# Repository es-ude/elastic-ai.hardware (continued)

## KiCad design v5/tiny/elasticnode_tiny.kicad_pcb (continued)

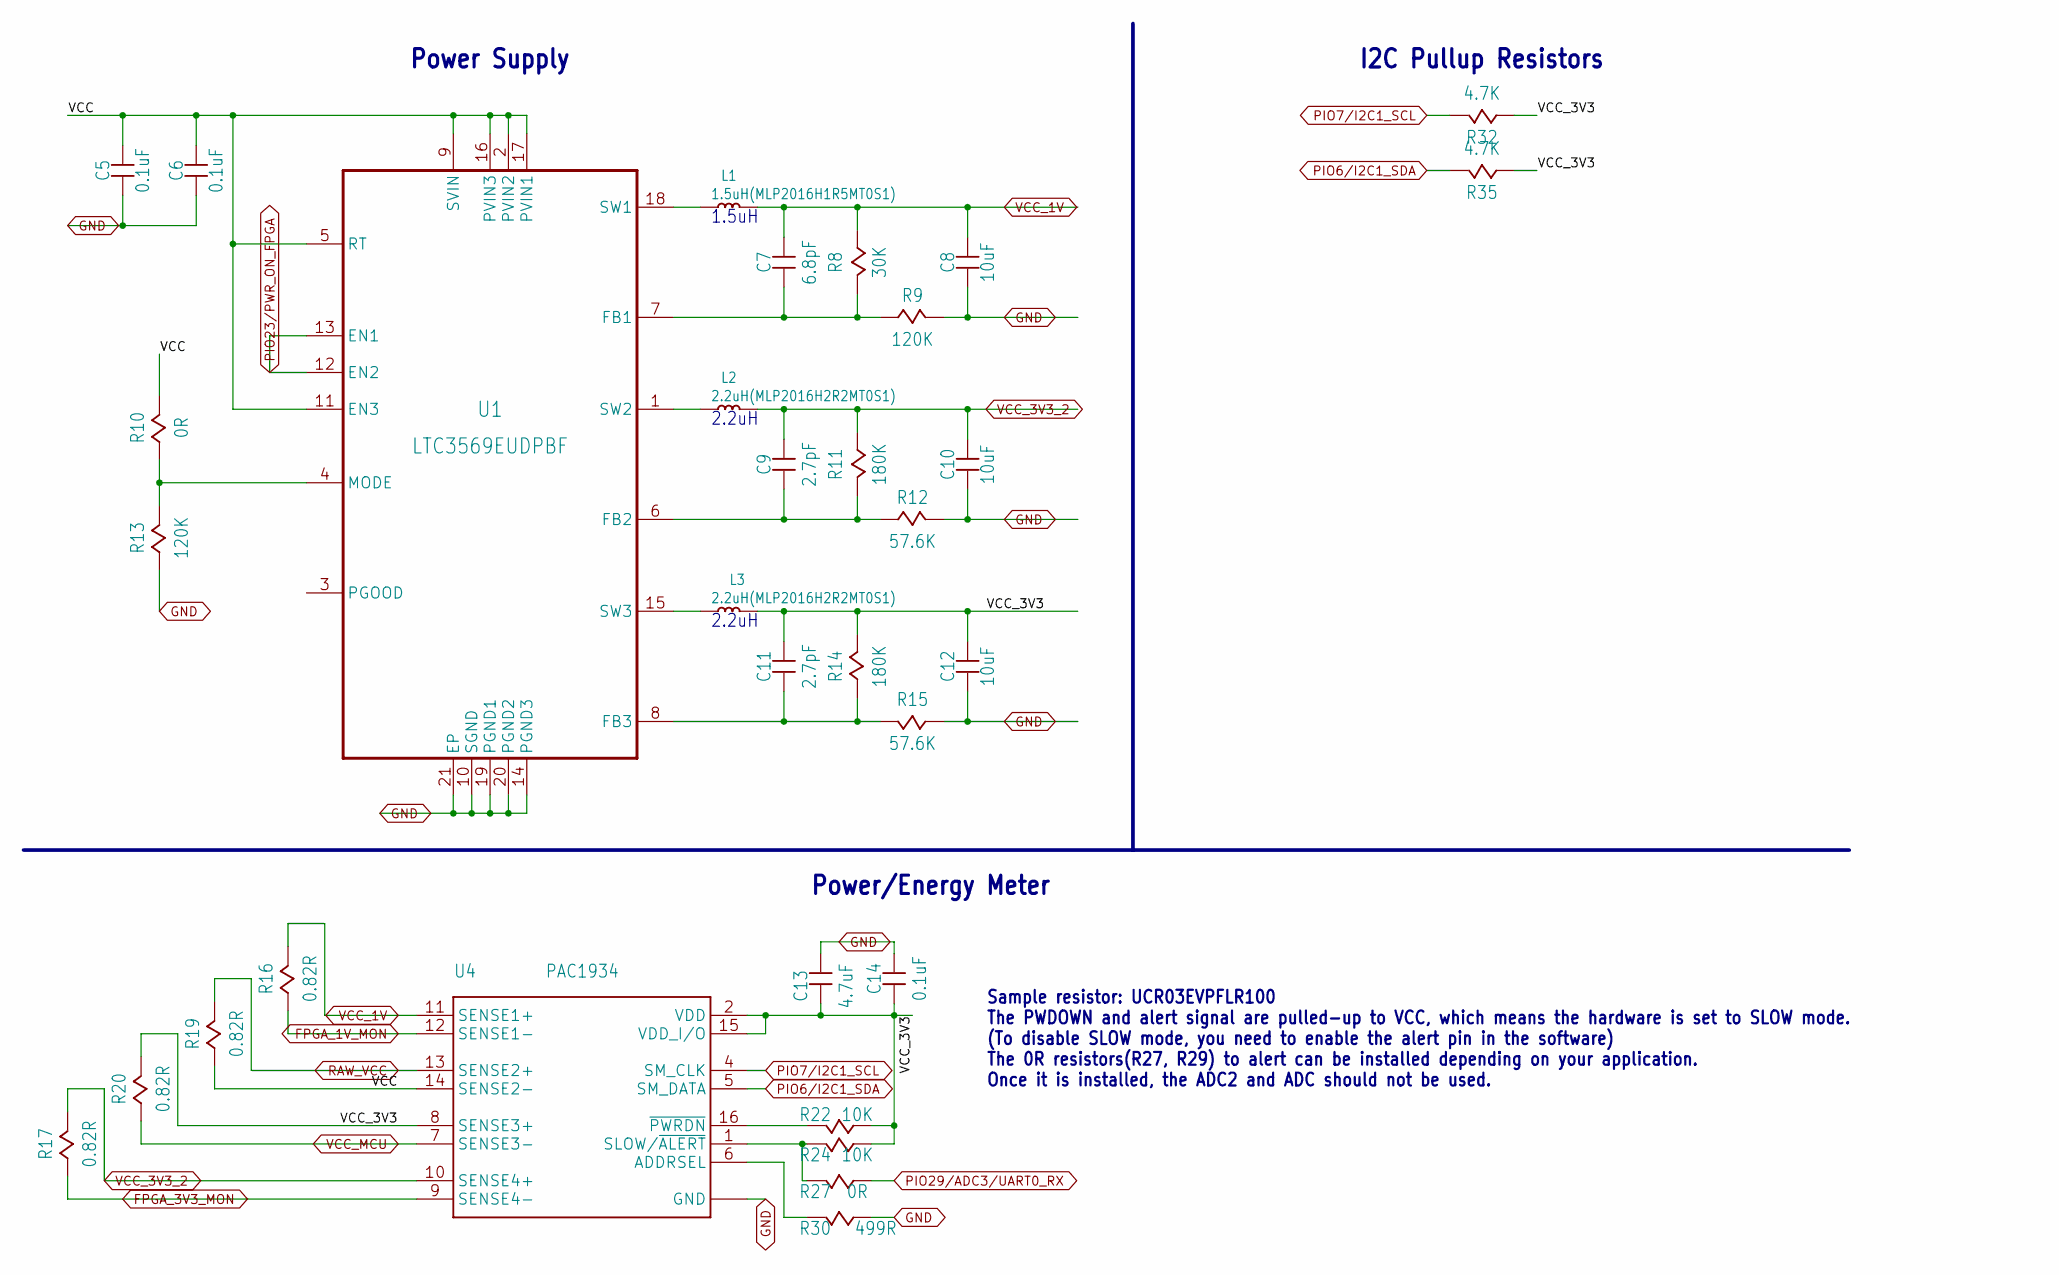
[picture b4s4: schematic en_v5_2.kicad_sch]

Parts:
C5, C6: 0.1uF; CAPC1608-0603
C7: 6.8pF; 0402
C8, C10, C12: 10uF; CAPC1608-0603
C9, C11: 2.7pF; 0402
C13: 4.7uF; CAPC1608-0603
C14: 0.1uF; 0402
L1: 1.5uH(MLP2016H1R5MT0S1); INDC2016X120N
L2, L3: 2.2uH(MLP2016H2R2MT0S1); INDC2016X120N
R8: 30K; 0402
R9, R13: 120K; 0402
R10, R27: 0R; 0402
R11, R14: 180K; 0402
R12, R15: 57.6K; 0402
R16, R17, R19, R20: 0.82R; 0603
R22, R24: 10K; 0402
R30: 499R; 0402
R32, R35: 4.7K; 0402
U1: LTC3569EUDPBF; QFN40P300X300X80-21N
U4: PAC1934; UQFN-16(4×4×0.5MM)

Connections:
FPGA_1V_MON: R16.1, U4.12 (SENSE1-); also elsewhere on the board
FPGA_3V3_MON: R17.1, U4.9 (SENSE4-); also elsewhere on the board
GND: C5.2, C6.2, C8.1, C10.2, C12.2, C13.2, C14.2, R9.2, R12.2, R13.1, R15.2, R30.1, U1.10 (SGND), U1.14 (PGND3), U1.19 (PGND1), U1.20 (PGND2), U1.21 (EP), U4.3 (GND), U4.17 (GND); also elsewhere on the board
unnamed: L2.1, U1.1 (SW2)
unnamed: L1.1, U1.18 (SW1)
unnamed: C7.2, R8.2, R9.1, U1.7 (FB1)
unnamed: L3.2, U1.15 (SW3)
unnamed: C11.2, R14.2, R15.1, U1.8 (FB3)
unnamed: C9.2, R11.2, R12.1, U1.6 (FB2)
unnamed: R24.2, R27.2, U4.1 (SLOW/~ALERT)
unnamed: R10.1, R13.2, U1.4 (MODE)
unnamed: R22.2, U4.16 (~PWRDN)
unnamed: R30.2, U4.6 (ADDRSEL)
PIO6/I2C1_SDA: R35.2, U4.5 (SM_DATA); also elsewhere on the board
PIO7/I2C1_SCL: R32.2, U4.4 (SM_CLK); also elsewhere on the board
PIO23/PWR_ON_FPGA: U1.12 (EN2), U1.13 (EN1); also elsewhere on the board
PIO29/ADC3/UART0_RX: R27.1; also elsewhere on the board
RAW_VCC: R19.2, U4.13 (SENSE2+); also elsewhere on the board
VCC: C5.1, C6.1, R10.2, R19.1, U1.2 (PVIN2), U1.5 (RT), U1.9 (SVIN), U1.11 (EN3), U1.16 (PVIN3), U1.17 (PVIN1), U4.14 (SENSE2-)
VCC_1V: C7.1, C8.2, L1.2, R8.1, R16.2, U4.11 (SENSE1+); also elsewhere on the board
VCC_3V3: C11.1, C12.1, C13.1, C14.1, L3.1, R14.1, R20.2, R22.1, R24.1, R32.1, R35.1, U4.2 (VDD), U4.8 (SENSE3+), U4.15 (VDD_I/O)
VCC_3V3_2: C9.1, C10.1, L2.2, R11.1, R17.2, U4.10 (SENSE4+); also elsewhere on the board
VCC_MCU: R20.1, U4.7 (SENSE3-); also elsewhere on the board

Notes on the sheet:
2.2uH
Sample resistor: UCR03EVPFLR100 The PWDOWN and alert signal are pulled-up to VCC, which means the hardware is set to SLOW mode. (To disable SLOW mode, you need to enable the alert pin in the software) The 0R resistors(R27, R29) to alert can be installed depending on your application. Once it is ins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
1.5uH
I2C Pullup Resistors
Power Supply
Power/Energy Meter

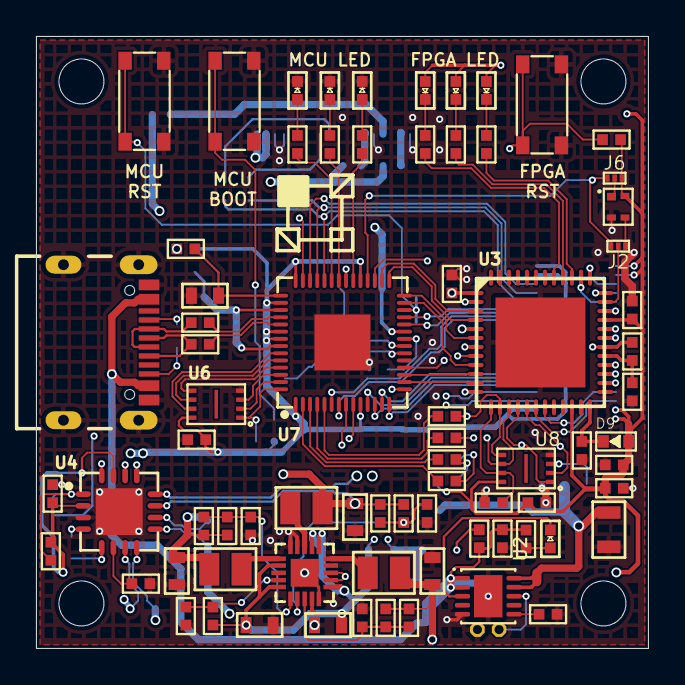
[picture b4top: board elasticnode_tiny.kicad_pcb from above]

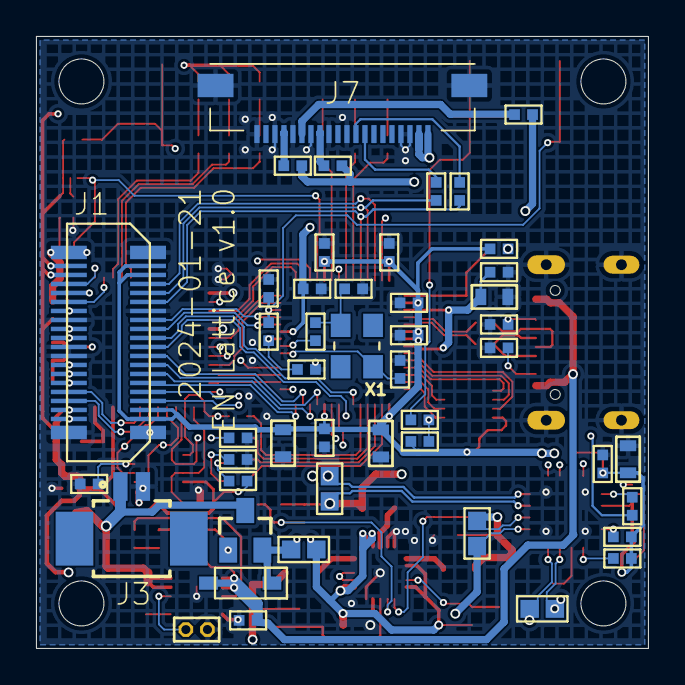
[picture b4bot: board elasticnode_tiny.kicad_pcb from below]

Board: 4 copper layers, 34.0 x 34.0 mm, 125 parts (47 on the bottom side), 114 nets.

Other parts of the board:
UNK_HOLE_0: dummyfp0
UNK_HOLE_1: dummyfp1
UNK_HOLE_2: dummyfp2
UNK_HOLE_3: dummyfp3

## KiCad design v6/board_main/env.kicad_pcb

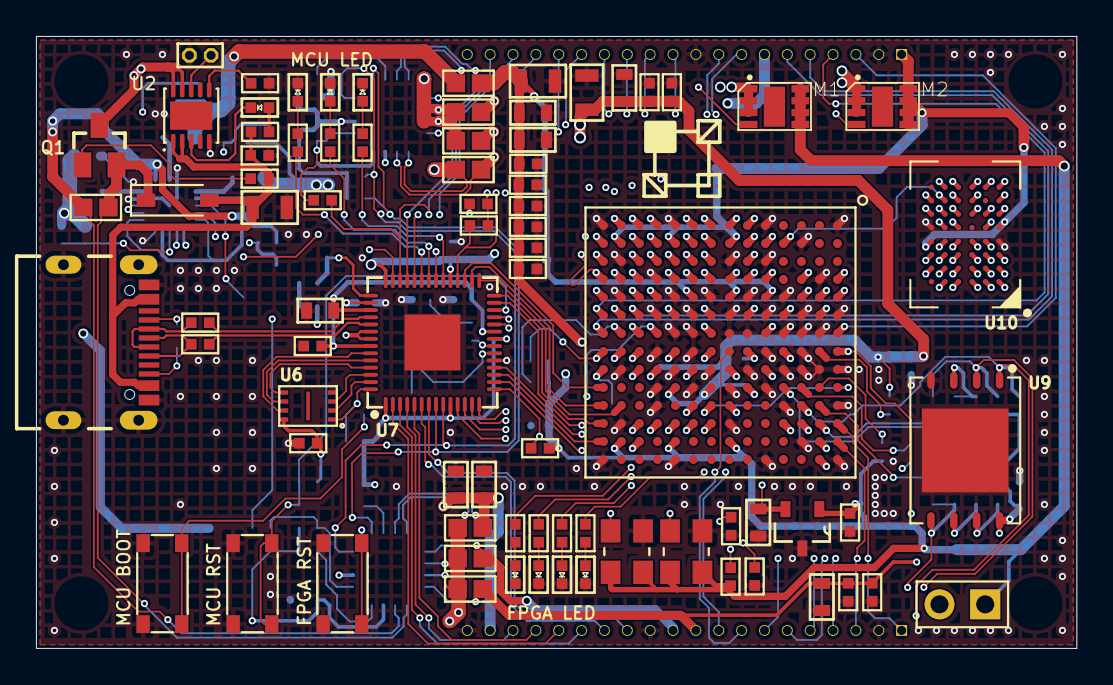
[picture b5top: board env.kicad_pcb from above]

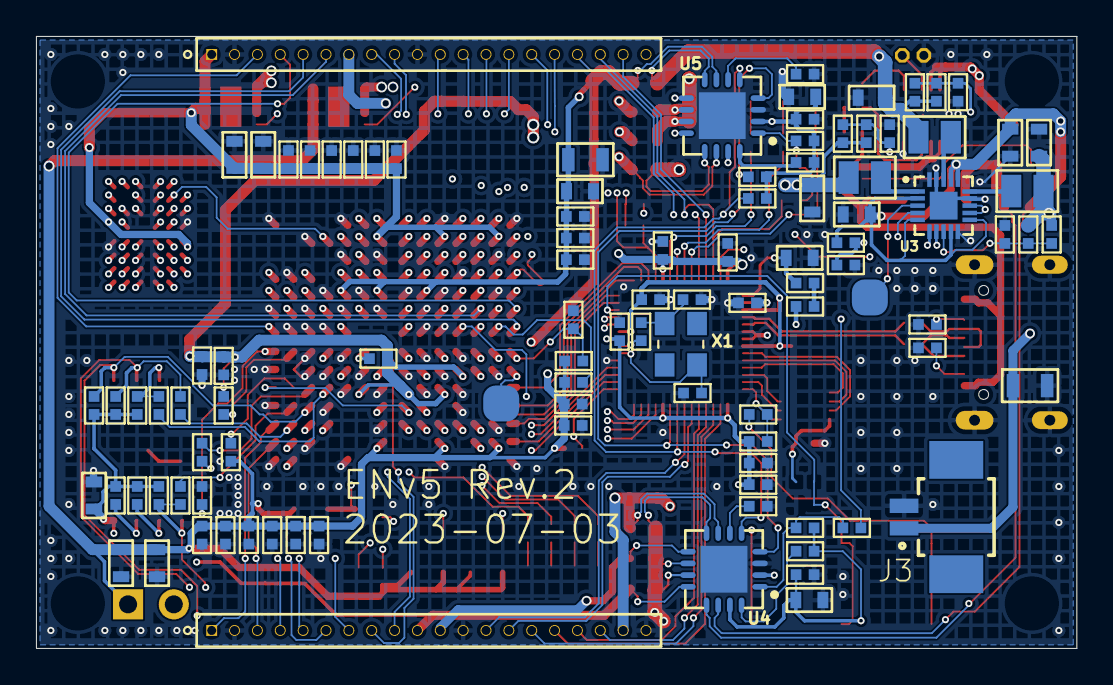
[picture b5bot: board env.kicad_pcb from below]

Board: 4 copper layers, 57.8 x 34.0 mm, 181 parts (102 on the bottom side), 171 nets.

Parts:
C1: 0.1uF; 0805
C2: 10uF; 0805
C3, C14, C16, C18, C19, C20, C21, C22, C23, C24, C26, C30, C44: 0.1uF; 0402
C4, C8, C10, C12, C42: 10uF; CAPC1608-0603
C5, C6: 0.1uF; CAPC1608-0603
C7: 6.8pF; 0402
C9: 3.3pF; 0402
C11: 2.7pF; 0402
C13, C15, C17, C25, C28, C29, C34, C35, C45, C46, C54, C60, C61, C68, C70: 4.7uF; CAPC1608-0603
C31, C32: 20pF; 0402
C33, C43: 1uF; 0402
C36, C37, C38, C39, C47, C48, C49, C50, C55, C56, C62, C63, C64, C71, C74: 470nF; 0402
C40, C41, C51, C52, C57, C58, C65, C66, C67, C72, C73, C75: 47nF; 0402
C53, C69: 47uF; 0805
C59: 100uF; 0805
D1: DIODEB5817W; SOD-123
D2: green; 0402
D3, D4, D5, D6, D7, D8, D9: red; 0402
J1, J2: M50-3142045THT; 20X1_HEADER_THT_1.27MM
J3: 53261-0271; MOLEX_53261-0271
J4: USB4105-GF-A; GCT_USB4105-GF-A
J5: FEMALE_HEADER_2X1; 2X1_HEADER
L1: 1.5uH(MLP2016H1R5MT0S1); INDC2016X120N
L2: 3.3uH(MLP2016H3R3MT0S1); INDC2016X120N
L3: 2.2uH(MLP2016H2R2MT0S1); INDC2016X120N
M1, M2: SISS23DN; POWERPAK1212-8
Q1: FDN302P; SSOT-3_402
R1, R2: 5K; 0402
R3, R22, R23, R24, R25, R34, R44: 10K; 0402
R4, R10, R27, R29, R47, R48, R49: 0R; 0402
R5, R45, R50, R53, R56, R57, R58: 2K; 0402
R6, R46, R51, R52, R54, R55, R62: 1K; 0402
R7: NTCLE413E2103H400; THT_2
R8: 30K; 0402
R9, R12, R13: 120K; 0402
R11: 150K; 0402
R14: 180K; 0402
R15: 57.6K; 0402
R16, R17, R18, R19, R20, R21, R26, R28: 0.82R; 0603
R30, R36, R38, R40, R63, R64, R67, R69: 499R; 0402
R31: 806R; 0402
R32, R35, R59: 4.7K; 0402
R33, R60, R61, R65, R66, R68, R70: 100R; 0402
R37: 200R; 0402
R41: 1R; 0402
R42, R43: 27R; 0402
S1, S2, S3: TACTILE-SWITCH
TP1, TP2: TEST_POINTSMD; SMD_PAD
U1: REF3012AIDBZR; SOT-23(3PIN)
U2: MCP73833T-AMI/MF; DFN-10(3X3X0.9)
U3: LTC3569EUDPBF; QFN40P300X300X80-21N
U4, U5: PAC1934; UQFN-16(4×4×0.5MM)
U6: W25Q16JVUXIQ; USON8-2X3MM
U7: RP2040; QFN40P700X700X100-57T310N
U8: SPARTAN7-LX15; FTGB196
U9: S25FL256S; WSON6X8MM
U10: CY7C1051DV33; BGA-48
X1: 12MHz; 3.2X2.5_OSC
X2: 32MHz; 3.2X2.5_OSC
X3: 100MHz; 3.2X2.5_OSC

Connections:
/FPGA/FPGA_DONE: TP1.1 (>NAME), U8.P9 (DONE_0)
/FPGA/FPGA_INT_B: C33.2, R50.2, U8.P8 (INIT_B_0)
/FPGA/PUDC_B: R51.1, U8.B10 (IO_L3P_T0_DQS_PUDC_B_14)
/MCU/ADC_AVDD: C28.1, R41.1, U7.43 (ADC_AVDD)
/MCU/MCU_1V1: C24.1, C25.1, C26.2, U7.23 (DVDD@1), U7.45 (VREG_VOUT), U7.50 (DVDD@2)
/MCU/MCU_QSPI_SCLK: U6.6 (CLK), U7.52 (QSPI_SCLK)
/MCU/MCU_QSPI_SD0: U6.5 (DI/IO0), U7.53 (QSPI_SD0)
/MCU/MCU_QSPI_SD1: U6.2 (DO/IO1), U7.55 (QSPI_SD1)
/MCU/MCU_QSPI_SD2: U6.3 (~WP/IO2), U7.54 (QSPI_SD2)
/MCU/MCU_QSPI_SD3: U6.7 (~HOLD/IO3), U7.51 (QSPI_SD3)
/MCU/MCU_QSPI_SS: R44.1, R45.2, U6.1 (~CS), U7.56 (QSPI_SS_N)
/MCU/MCU_USB_D_N: R43.1, U7.46 (USB_DM)
/MCU/MCU_USB_D_P: R42.1, U7.47 (USB_DP)
/MCU/PIO22/LED0: R36.1, U7.34 (GPIO22)
/MCU/PIO24/LED1: R38.1, U7.36 (GPIO24)
/MCU/PIO25/LED2: R40.1, U7.37 (GPIO25)
/MCU/~MCU_RST: S1.3 (2), S1.4 (2), U7.26 (RUN)
/MCU/~USB_BOOT: R45.1, S2.1, S2.2 (1)
/Power Sensing/FPGA_VCCIO_MON: M1.1 (S), M1.2 (S), M1.3 (S), R17.1, U5.12 (SENSE1-)
/Power Sensing/FPGA_VCC_SRAM_MON: M2.1 (S), M2.2 (S), M2.3 (S), R28.1, U5.9 (SENSE4-)
/Power Sensing/~EN_PWR_SRAM: M2.4 (G), R33.1, R34.2
/Power Supply/PGOOD: TP2.1 (>NAME), U3.3 (PGOOD)
/SRAM_Flash/SPI2FLASH_DQ2: R56.2, R68.2, U9.3 (~WP/IO2)
/SRAM_Flash/SPI2FLASH_DQ3: R53.2, R70.2, U9.7 (~HOLD/IO3)
FADC_VN: J1.9, U8.H7 (VN_0)
FADC_VP: J1.8, U8.G8 (VP_0)
FIO_0: J1.1, U8.A12 (IO_L4P_T0_D04_14)
FIO_1: J1.3, U8.A13 (IO_L4N_T0_D05_14)
FIO_2: J1.4, U8.B13 (IO_L5P_T0_D06_14)
FIO_3: J1.5, U8.C12 (IO_L6N_T0_D08_VREF_14)
FIO_4: J1.6, U8.B14 (IO_L5N_T0_D07_14)
FIO_5: J1.7, U8.D12 (IO_L8P_T1_D11_14)
FLASH_DQ0: R65.1, U8.B11 (IO_L1P_T0_D00_MOSI_14)
FLASH_DQ1: R66.1, U8.B12 (IO_L1N_T0_D01_DIN_14)
FLASH_DQ2: R68.1, U8.D10 (IO_L2P_T0_D02_14)
FLASH_DQ3: R70.1, U8.C10 (IO_L2N_T0_D03_14)
FPGA_LED0: R63.1, U8.H12 (IO_L13N_T2_MRCC_14)
FPGA_LED1: R64.1, U8.J12 (IO_L17N_T2_D29_14)
FPGA_LED2: R67.1, U8.K12 (IO_L19N_T3_D25_VREF_14)
FPGA_LED3: R69.1, U8.J11 (IO_L17P_T2_D30_14)
FPGA_M0: R55.2, U8.M7 (M0_0)
FPGA_M1: R54.2, U8.M8 (M1_0)
FPGA_M2: J5.3 (2), R52.2, U8.M9 (M2_0)
FPGA_VCC_1V: C59.2, C60.2, C61.2, C62.2, C63.2, C64.2, C65.2, C66.2, C67.2, C69.2, C70.2, C71.2, C72.2, C73.2, R21.1, U5.7 (SENSE3-), U8.D6 (VCCINT), U8.D8 (VCCINT), U8.E5 (VCCBRAM), U8.E7 (VCCINT), U8.E9 (VCCINT), U8.F6 (VCCINT), U8.G5 (VCCBRAM), U8.G9 (VCCINT), U8.H6 (VCCINT), U8.J5 (VCCBRAM), U8.J9 (VCCINT), U8.K6 (VCCINT), U8.K8 (VCCINT)
FPGA_VCC_1V8: C53.2, C54.2, C55.2, C56.2, C57.2, C58.2, R18.1, R47.2, R48.2, U5.14 (SENSE2-), U8.F10 (VCCAUX), U8.H10 (VCCAUX), U8.K10 (VCCAUX), U8.L9 (VCCAUX)
GCLK_32: U8.G11 (IO_L12P_T1_MRCC_14), X2.3 (OUTPUT)
GCLK_100: U8.A10 (IO_L3N_T0_DQS_EMCCLK_14), U8.H11 (IO_L13P_T2_MRCC_14), X3.3 (OUTPUT)
GND: C1.1, C2.2, C3.1, C4.1, C5.2, C6.2, C8.1, C10.2, C12.2, C13.2, C14.2, C15.2, C16.2, C17.2, C18.1, C19.2, C20.2, C21.2, C22.2, C23.2, C24.2, C25.2, C26.1, C28.2, C29.2, C30.2, C31.2, C32.2, C33.1, C34.1, C35.1, C36.1, C37.1, C38.1, C39.1, C40.1, C41.1, C42.1, C43.1, C44.1, C45.1, C46.1, C47.1, C48.1, C49.1, C50.1, C51.1, C52.1, C53.1, C54.1, C55.1, C56.1, C57.1, C58.1, C59.1, C60.1, C61.1, C62.1, C63.1, C64.1, C65.1, C66.1, C67.1, C68.2, C69.1, C70.1, C71.1, C72.1, C73.1, C74.1, C75.1, D3.2, D4.2, D5.2, D6.2, D7.2, D8.2, D9.2, J1.2, J1.12, J1.20, J2.2, J2.10, J3.2, J4.A1_B12 (GND), J4.B1_A12 (GND), J4.S1 (SHELL_GND), J4.S2 (SHELL_GND), J4.S3 (SHELL_GND), J4.S4 (SHELL_GND), R1.2, R2.1, R3.2, R5.2, R7.P$1 (1), R9.2, R12.2, R13.1, R15.2, R30.1, R31.1, R52.1, R54.1, R61.2, S1.1, S1.2 (1), S2.3 (2), S2.4 (2), S3.3 (2), S3.4 (2), U1.3 (GND), U2.5 (VSS), U2.11 (EXP), U3.10 (SGND), U3.14 (PGND3), U3.19 (PGND1), U3.20 (PGND2), U3.21 (EP), U4.3 (GND), U4.17 (GND), U5.3 (GND), U5.17 (GND), U6.4 (GND), U7.19 (TESTEN), U7.57 (GND), U8.A1 (GND), U8.A6 (GND), U8.A9 (GND), U8.A11 (GND), U8.A14 (GND), U8.B4 (GND), U8.B7 (GND), U8.B9 (GND), U8.C2 (GND), U8.C6 (GND), U8.C7 (GND), U8.C8 (GND), U8.C9 (GND), U8.C13 (GND), U8.D5 (GND), U8.D7 (GND), U8.D9 (GND), U8.D11 (GND), U8.E1 (GND), U8.E3 (GND), U8.E6 (GND), U8.E8 (GND), U8.E10 (GND), U8.E14 (GND), U8.F5 (GND), U8.F7 (GNDADC_0), U8.F9 (GND), U8.G3 (GND), U8.G6 (GND), U8.G7 (VREFN_0), U8.G10 (GND), U8.G12 (GND), U8.H5 (GND), U8.H9 (GND), U8.J6 (GND), U8.J7 (DXN_0), U8.J8 (DXP_0), U8.J10 (GND), U8.K1 (GND), U8.K5 (GND), U8.K7 (GND), U8.K9 (GND), U8.K14 (GND), U8.L4 (GND), U8.L6 (GND), U8.L8 (GND), U8.L10 (GND), U8.L11 (GND), U8.N3 (GND), U8.N5 (GND), U8.N9 (GND), U8.N12 (GND), U8.P1 (GND), U8.P14 (GND), U9.4 (VSS), U9.9 (VSS), U10.D1 (VSS), U10.E6 (VSS), X2.2 (GND), X3.2 (GND)
JTAG_TCK: J2.3, U8.A7 (TCK_0)
JTAG_TDI: J2.5, U8.P7 (TDI_0)
JTAG_TDO: J2.4, U8.P6 (TDO_0)
JTAG_TMS: J2.6, U8.M6 (TMS_0)
unnamed: C7.2, R8.2, R9.1, U3.7 (FB1)
unnamed: C9.2, R11.2, R12.1, U3.6 (FB2)
unnamed: C11.2, R14.2, R15.1, U3.8 (FB3)
unnamed: C31.1, U7.20 (XIN), X1.1
unnamed: C32.1, R46.2, X1.3
unnamed: D2.1, R6.2
unnamed: D3.1, R36.2
unnamed: D4.1, R38.2
unnamed: D5.1, R40.2
unnamed: D6.1, R63.2
unnamed: D7.1, R64.2
unnamed: D8.1, R67.2
unnamed: D9.1, R69.2
unnamed: J4.A5 (CC1), R1.1
unnamed: J4.B5 (CC2), R2.2
unnamed: L1.1, U3.18 (SW1)
unnamed: L2.1, U3.1 (SW2)
unnamed: L3.2, U3.15 (SW3)
unnamed: Q1.1 (G), R4.1
unnamed: R7.P$2 (2), U2.8 (THERM)
unnamed: R37.1, R41.2
unnamed: R5.1, U2.6 (PROG)
unnamed: D2.2, U2.3 (STAT1)
unnamed: R10.1, R13.2, U3.4 (MODE)
unnamed: R30.2, U4.6 (ADDRSEL)
unnamed: R24.2, R27.2, U4.1 (SLOW/~ALERT)
unnamed: R22.2, U4.16 (~PWRDN)
unnamed: R31.2, U5.6 (ADDRSEL)
unnamed: R25.2, R29.2, U5.1 (SLOW/~ALERT)
unnamed: R23.2, U5.16 (~PWRDN)
unnamed: R46.1, U7.21 (XOUT)
unnamed: R49.1, U8.N7 (CFGBVS_0)
unnamed: R48.1, U8.F8 (VCCADC_0)
unnamed: R47.1, U8.B8 (VCCBAT)
unnamed: U10.A6 (NC), U10.E3 (NC), U10.G2 (NC), U10.H6 (NC)
PIO0/SPI2FLASH_MISO(SPI0): J1.16, R57.2, R66.2, U7.2 (GPIO0), U9.2 (SO/IO1)
PIO1/SPI2FLASH_CS(SPI0): J1.15, R59.2, U7.3 (GPIO1), U8.C11 (IO_L6P_T0_FCS_B_14), U9.1 (~CS)
PIO2/SPI2FLASH_SCK(SPI0): J1.18, R60.2, R61.1, U7.4 (GPIO2), U8.A8 (CCLK_0), U9.6 (SCK)
PIO3/SPI2FLASH_MOSI(SPI0): J1.17, R58.2, R65.2, U7.5 (GPIO3), U9.5 (SI/IO0)
PIO4/UART1_TX: J1.14, U7.6 (GPIO4)
PIO5/UART1_RX: J1.13, U7.7 (GPIO5)
PIO6/I2C1_SDA: J2.16, R35.2, U4.5 (SM_DATA), U5.5 (SM_DATA), U7.8 (GPIO6)
PIO7/I2C1_SCL: J2.15, R32.2, U4.4 (SM_CLK), U5.4 (SM_CLK), U7.9 (GPIO7)
PIO8/SPI_MISO(SPI1)/I2C0_SDA: J2.11, U7.11 (GPIO8)
PIO9/SPI_NSS(SPI1)/I2C0_SCL: J2.12, U7.12 (GPIO9)
PIO10/SPI_SCK(SPI1)/I2C1SDA: J2.13, U7.13 (GPIO10)
PIO11/SPI_MOSI/I2C1SCL: J2.14, U7.14 (GPIO11)
PIO12/~FPGA_RESET: R62.1, S3.1, S3.2 (1), U7.15 (GPIO12), U8.L7 (PROGRAM_B_0)
PIO13/GPIO2FPGA_0: U7.16 (GPIO13), U8.M13 (IO_L15P_T2_DQS_RDWR_B_14)
PIO14/GPIO2FPGA_1: U7.17 (GPIO14), U8.P13 (IO_L22N_T3_D20_14)
PIO15/GPIO2FPGA_2: U7.18 (GPIO15), U8.L12 (IO_L16P_T2_CSI_B_14)
PIO16/SPI2FPGA_MISO: U7.27 (GPIO16), U8.M12 (IO_L20N_T3_D23_14)
PIO17/SPI2FPGA_CS: U7.28 (GPIO17), U8.P12 (IO_L22P_T3_D21_14)
PIO18/SPI2FPGA_SCK: U7.29 (GPIO18), U8.N11 (IO_L23N_T3_D18_14)
PIO19/SPI2FPGA_MOSI: U7.30 (GPIO19), U8.P11 (IO_L24N_T3_D16_14)
PIO20/GPIO2FPGA_3: U7.31 (GPIO20), U8.P10 (IO_L24P_T3_D17_14)
PIO21/~PWR_FPGA_IO_SRAM: M1.4 (G), R33.2, U7.32 (GPIO21)
PIO23/PWR_ON_1V8_1V: U3.12 (EN2), U3.13 (EN1), U7.35 (GPIO23)
PIO26/ADC0: J2.20, U7.38 (GPIO26_ADC0)
PIO27/ADC1: J2.19, U7.39 (GPIO27_ADC1)
PIO28/ADC2/UART0_TX: J2.18, R29.1, U7.40 (GPIO28_ADC2)
PIO29/ADC3/UART0_RX: J2.17, R27.1, U7.41 (GPIO29_ADC3)
RAW_VCC: D1.1 (C), Q1.2 (S), R19.2, U4.13 (SENSE2+)
SRAM_A0: U8.F1 (IO_L9N_T1_DQS_34), U10.A3 (A0)
SRAM_A1: U8.J3 (IO_L17N_T2_34), U10.A4 (A1)
SRAM_A2: U8.G4 (IO_L12P_T1_MRCC_34), U10.A5 (A2)
SRAM_A3: U8.F2 (IO_L8N_T1_34), U10.B3 (A3)
SRAM_A4: U8.H4 (IO_L13P_T2_MRCC_34), U10.B4 (A4)
SRAM_A5: U8.F3 (IO_L8P_T1_34), U10.C3 (A5)
SRAM_A6: U8.H1 (IO_L14N_T2_SRCC_34), U10.C4 (A6)
SRAM_A7: U8.G1 (IO_L9P_T1_DQS_34), U10.D4 (A7)
SRAM_A8: U8.L3 (IO_L22P_T3_34), U10.H2 (A8)
SRAM_A9: U8.L2 (IO_L22N_T3_34), U10.H3 (A9)
SRAM_A10: U8.P3 (IO_L21N_T3_DQS_34), U10.H4 (A10)
SRAM_A11: U8.M5 (IO_L23P_T3_34), U10.H5 (A11)
SRAM_A12: U8.L1 (IO_L18N_T2_34), U10.G3 (A12)
SRAM_A13: U8.P4 (IO_L21P_T3_DQS_34), U10.G4 (A13)
SRAM_A14: U8.K4 (IO_L16P_T2_34), U10.F3 (A14)
SRAM_A15: U8.P5 (IO_L24P_T3_34), U10.F4 (A15)
SRAM_A16: U8.P2 (IO_L20P_T3_34), U10.E4 (A16)
SRAM_A17: U8.F4 (IO_L12N_T1_MRCC_34), U10.D3 (A17)
SRAM_A18: U8.M1 (IO_L18P_T2_34), U10.H1 (A18)
SRAM_BHE: U8.A5 (IO_L4N_T0_34), U10.B2 (~BHE)
SRAM_BLE: U8.C4 (IO_L6N_T0_VREF_34), U10.A1 (~BLE)
SRAM_CE: U8.H3 (IO_L13N_T2_MRCC_34), U10.B5 (~CE)
SRAM_D0: U8.J2 (IO_L15P_T2_DQS_34), U10.B6 (D0)
SRAM_D1: U8.H2 (IO_L14P_T2_SRCC_34), U10.C5 (D1)
SRAM_D2: U8.J1 (IO_L15N_T2_DQS_34), U10.C6 (D2)
SRAM_D3: U8.E2 (IO_L10P_T1_34), U10.D5 (D3)
SRAM_D4: U8.J4 (IO_L17P_T2_34), U10.E5 (D4)
SRAM_D5: U8.N4 (IO_L24N_T3_34), U10.F5 (D5)
SRAM_D6: U8.M4 (IO_L23N_T3_34), U10.F6 (D6)
SRAM_D7: U8.N1 (IO_L20N_T3_34), U10.G6 (D7)
SRAM_D8: U8.B5 (IO_L4P_T0_34), U10.B1 (D8)
SRAM_D9: U8.B6 (IO_0_34), U10.C1 (D9)
SRAM_D10: U8.C5 (IO_L6P_T0_34), U10.C2 (D10)
SRAM_D11: U8.E4 (IO_L7P_T1_34), U10.D2 (D11)
SRAM_D12: U8.K3 (IO_L16N_T2_34), U10.E2 (D12)
SRAM_D13: U8.L5 (IO_25_34), U10.F2 (D13)
SRAM_D14: U8.M2 (IO_L19N_T3_VREF_34), U10.F1 (D14)
SRAM_D15: U8.M3 (IO_L19P_T3_34), U10.G1 (D15)
SRAM_OE: U8.A4 (IO_L2P_T0_34), U10.A2 (~OE)
SRAM_WE: U8.D2 (IO_L10N_T1_34), U10.G5 (~WE)
SWCLK: J2.8, U7.24 (SWCLK)
SWDIO: J2.9, U7.25 (SWDIO)
USB_D_N: J4.A7 (DN1), J4.B7 (DN2), R43.2
USB_D_P: J4.A6 (DP1), J4.B6 (DP2), R42.2
VBAT: C2.1, J3.1, Q1.3 (D), U2.9 (VBAT), U2.10 (VBAT)
VBUS: C1.2, D1.2 (A), J4.A4_B9 (VBUS), J4.B4_A9 (VBUS), R3.1, R4.2, R6.1, U2.1 (VDD), U2.2 (VDD)
VCC: C5.1, C6.1, R10.2, R19.1, U3.2 (PVIN2), U3.5 (RT), U3.9 (SVIN), U3.11 (EN3), U3.16 (PVIN3), U3.17 (PVIN1), U4.14 (SENSE2-)
VCC_1V: C7.1, C8.2, L1.2, R8.1, R21.2, U5.8 (SENSE3+)
VCC_1V8: C9.1, C10.1, L2.2, R11.1, R18.2, U5.13 (SENSE2+)
VCC_3V3: C11.1, C12.1, C13.1, C14.1, C15.1, C16.1, L3.1, R14.1, R16.2, R17.2, R20.2, R22.1, R23.1, R24.1, R25.1, R26.2, R28.2, R32.1, R35.1, U4.2 (VDD), U4.8 (SENSE3+), U4.10 (SENSE4+), U4.11 (SENSE1+), U4.15 (VDD_I/O), U5.2 (VDD), U5.10 (SENSE4+), U5.11 (SENSE1+), U5.15 (VDD_I/O)
VCC_30_14: C3.2, C34.2, C35.2, C36.2, C37.2, C38.2, C39.2, C40.2, C41.2, C74.2, C75.2, J5.1, M1.5 (D), M1.6 (D), M1.7 (D), M1.8 (D), R49.2, R50.1, R51.2, R55.1, R62.2, U1.1 (IN), U8.G13 (VCCO_14), U8.K13 (VCCO_14), U8.N6 (VCCO_0), U8.N8 (VCCO_0), U8.N13 (VCCO_14), X2.1 (EN), X2.4 (VS+), X3.1 (EN), X3.4 (VS+)
VCC_30_34: C45.2, C46.2, C47.2, C48.2, C49.2, C50.2, C51.2, C52.2, J2.1, M2.5 (D), M2.6 (D), M2.7 (D), M2.8 (D), U8.G2 (VCCO_34), U8.K2 (VCCO_34), U8.N2 (VCCO_34), U10.D6 (VCC), U10.E1 (VCC)
VCC_MCU: C17.1, C18.2, C19.1, C20.1, C21.1, C22.1, C23.1, C29.1, C30.1, J1.19, J2.7, R20.1, R34.1, R37.2, R44.2, U4.7 (SENSE3-), U6.8 (VCC), U7.1 (IOVDD@1), U7.10 (IOVDD@2), U7.22 (IOVDD@3), U7.33 (IOVDD@4), U7.42 (IOVDD@5), U7.44 (VREG_VIN), U7.48 (USB_VDD), U7.49 (IOVDD@6)
VCC_SENSORS: C42.2, C43.2, C44.2, C68.1, J1.10, R16.1, R53.1, R56.1, R57.1, R58.1, R59.1, R60.1, U4.12 (SENSE1-), U9.8 (VCC)
VCC_WIRELESS: J1.11, R26.1, U4.9 (SENSE4-)
XADC_VREF: C4.2, U1.2 (OUT), U8.H8 (VREFP_0)

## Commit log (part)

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2025-12-09 Add dev_kit for ENv6
2025-12-09 Adapt numbers for easier ordering and assembling
2025-12-09 Tiny hardware design files
2026-01-10 Add right files to ENV6 dev
2026-01-14 Fixed DRC errors in dev board v6
2026-01-14 fixed isolated Cap GND in Dev-Artix
2026-01-19 Remove old artefacts and add mcu schematic to ENV6 main
2026-02-20 Rephrasing ENV5 design
2026-03-23 Add Schematic for 1st ENV6 DemoBoard
2026-03-25 ENV6 (test): Changes after first review
2026-04-11 new PSU and updates
2026-04-13 Remove backups and documents
2026-04-13 Changes after second rev of ENV6 test
2026-04-23 added comments
2026-05-22 Add design of ENV6 mini
2026-06-15 Add hardware for MXO4 setup
2026-06-17 update Demoboard and add GateMateA11 board
2026-06-24 Add comments for GateMAte board
